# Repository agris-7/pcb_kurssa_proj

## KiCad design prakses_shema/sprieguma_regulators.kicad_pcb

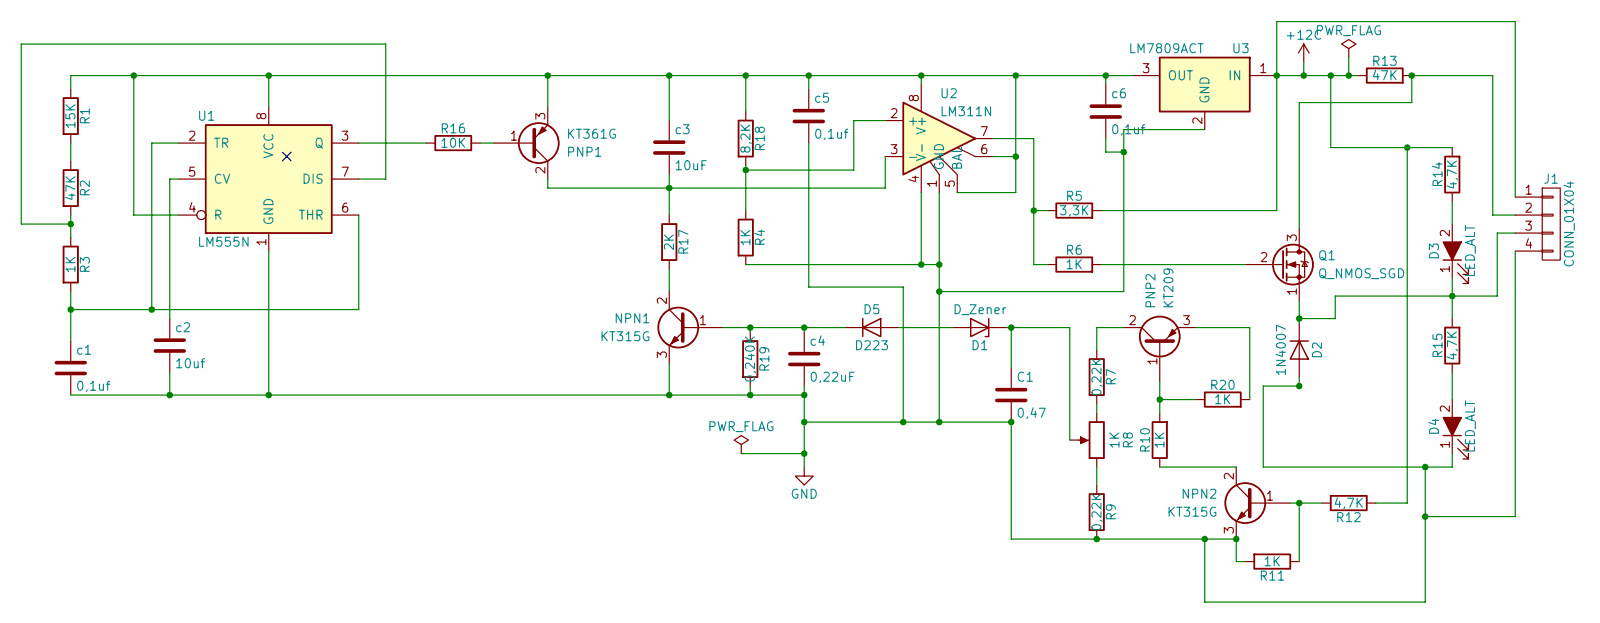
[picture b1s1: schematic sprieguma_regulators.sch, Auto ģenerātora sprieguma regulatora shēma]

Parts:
C1: 0,47; C_Disc_D7.5mm_W2.5mm_P5.00mm
D1: D_Zener; D_P600_R-6_P20.00mm_Horizontal
D2: 1N4007; D_DO-41_SOD81_P12.70mm_Horizontal
D3, D4: LED_ALT; LED_D5.0mm
D5: D223; D_A-405_P12.70mm_Horizontal
J1: CONN_01X04; Conector4pin
NPN1, NPN2: KT315G; TO-92_Inline_Wide
PNP1: KT361G; TO-92_Inline_Wide
PNP2: KT209; TO-92_Inline_Wide
Q1: Q_NMOS_SGD; TO-220_Vertical
R1: 15K; R_Axial_DIN0414_L11.9mm_D4.5mm_P20.32mm_Horizontal
R2, R13: 47K; R_Axial_DIN0414_L11.9mm_D4.5mm_P20.32mm_Horizontal
R3, R4, R6, R10, R11: 1K; R_Axial_DIN0414_L11.9mm_D4.5mm_P20.32mm_Horizontal
R5: 3,3K; R_Axial_DIN0207_L6.3mm_D2.5mm_P10.16mm_Horizontal
R7, R9: 0,22K; R_Axial_DIN0414_L11.9mm_D4.5mm_P25.40mm_Horizontal
R8: 1K; Potentiometer_Trimmer_Bourns_3266Z
R12, R14, R15: 4,7K; R_Axial_DIN0516_L15.5mm_D5.0mm_P25.40mm_Horizontal
R16: 10K; R_Axial_DIN0207_L6.3mm_D2.5mm_P10.16mm_Horizontal
R17: 2K; R_Axial_DIN0414_L11.9mm_D4.5mm_P20.32mm_Horizontal
R18: 8,2K; R_Axial_DIN0204_L3.6mm_D1.6mm_P7.62mm_Horizontal
R19: 0,240K; R_Axial_DIN0204_L3.6mm_D1.6mm_P7.62mm_Horizontal
R20: 1K; R_Axial_DIN0207_L6.3mm_D2.5mm_P10.16mm_Horizontal
U1: LM555N; DIP-8_W10.16mm
U2: LM311N; DIP-8_W10.16mm
U3: LM7809ACT; TO-220_Vertical
c1, c5, c6: 0,1uf; C_Disc_D4.7mm_W2.5mm_P5.00mm
c2: 10uf; C_Disc_D5.0mm_W2.5mm_P5.00mm
c3: 10uF; CP_Radial_D8.0mm_P2.50mm
c4: 0,22uF; C_Disc_D5.0mm_W2.5mm_P5.00mm

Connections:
+12C: J1.1, R5.2, R12.1, R13.1, R14.2, U3.1 (IN)
GND: C1.2, D2.2 (A), D4.1 (K), J1.4, NPN1.3 (E), NPN2.3 (E), R4.2, R9.2, R11.2, R19.2, U1.1 (GND), U2.1 (GND), U2.4 (V-), U3.2 (GND), c1.2, c2.2, c4.2, c5.2, c6.2
unnamed: C1.1, D1.1 (K), R8.2
unnamed: D1.2 (A), D5.2 (A)
unnamed: D2.1 (K), D3.1 (K), J1.3, Q1.1 (S), R15.2
unnamed: D3.2 (A), R14.1
unnamed: D4.2 (A), R15.1
unnamed: D5.1 (K), NPN1.1 (B), R19.1, c4.1
unnamed: J1.2, Q1.3 (D), R13.2
unnamed: NPN1.2 (C), R17.2
unnamed: NPN2.1 (B), R11.1, R12.2
unnamed: NPN2.2 (C), R10.1
unnamed: PNP1.1 (B), R16.2
unnamed: PNP1.2 (C), R17.1, U2.3 (-), c3.2
unnamed: PNP1.3 (E), R1.1, R18.1, U1.4 (R), U1.8 (VCC), U2.5 (BAL), U2.6, U2.8 (V+), U3.3 (OUT), c3.1, c5.1, c6.1
unnamed: PNP2.1 (B), R10.2, R20.1
unnamed: PNP2.2 (C), R7.1
unnamed: PNP2.3 (E), R20.2
unnamed: Q1.2 (G), R6.2
unnamed: R1.2, R2.1
unnamed: R2.2, R3.1, U1.7 (DIS)
unnamed: R3.2, U1.2 (TR), U1.6 (THR), c1.1
unnamed: R5.1, R6.1, U2.7
unnamed: R7.2, R8.3
unnamed: R8.1, R9.1
unnamed: R16.1, U1.3 (Q)
unnamed: R4.1, R18.2, U2.2 (+)
unnamed: U1.5 (CV), c2.1

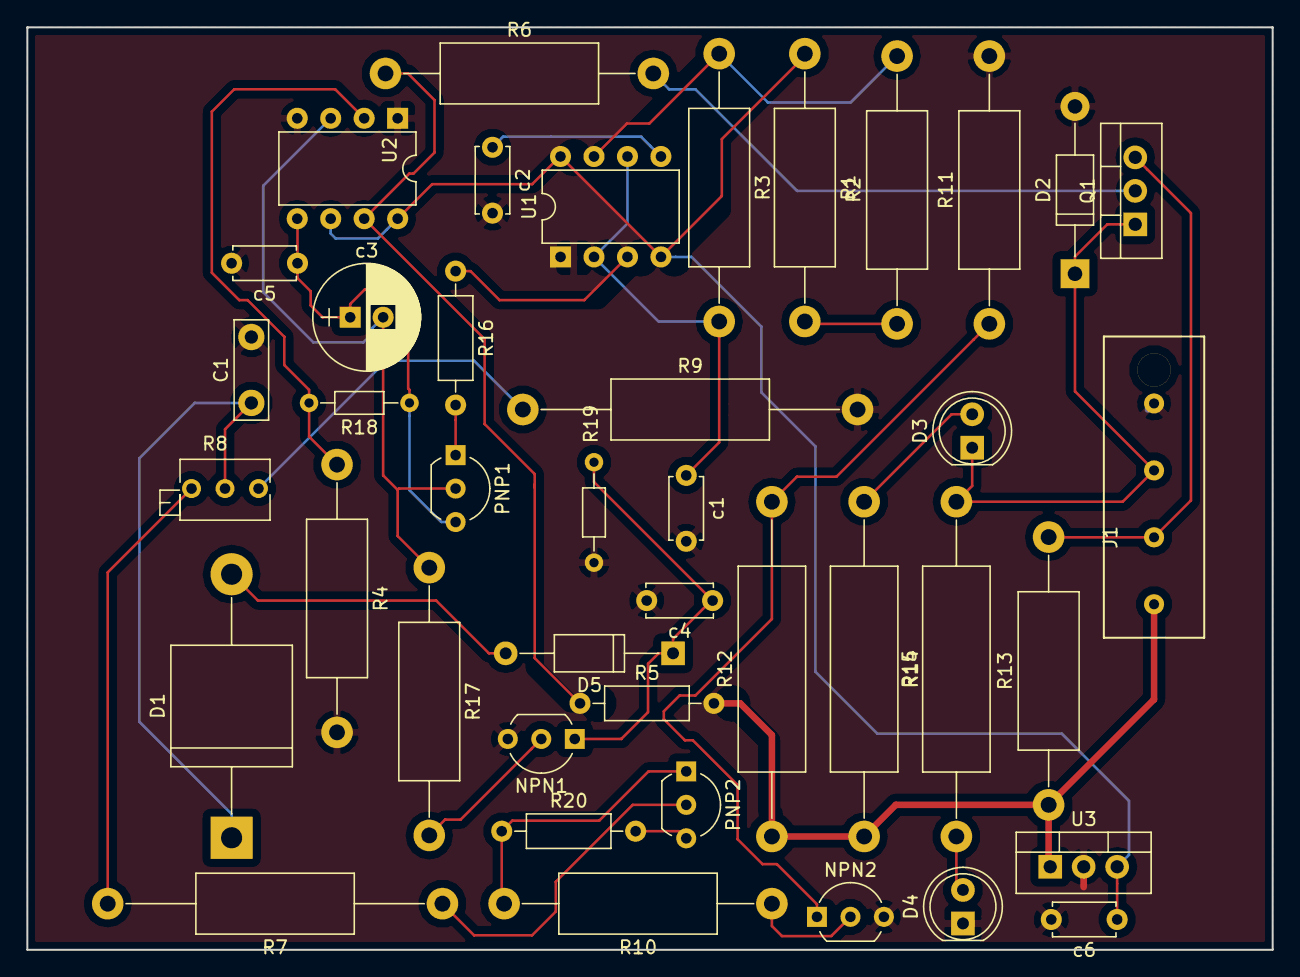
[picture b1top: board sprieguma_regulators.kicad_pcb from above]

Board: 2 copper layers, 94.5 x 70.0 mm, 41 parts (0 on the bottom side), 28 nets.

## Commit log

2017-03-26 Izveidots 2_MD
2017-03-26 pievienots 3md PWR_Supply
2017-03-26 pievienots 3md komponentu_saraksts
2017-03-29 pievienots 4md
2017-05-10 labots Power syply md
2017-05-25 gerberfails
2017-05-25 BOM atskaite
2017-06-17 kura darbs
